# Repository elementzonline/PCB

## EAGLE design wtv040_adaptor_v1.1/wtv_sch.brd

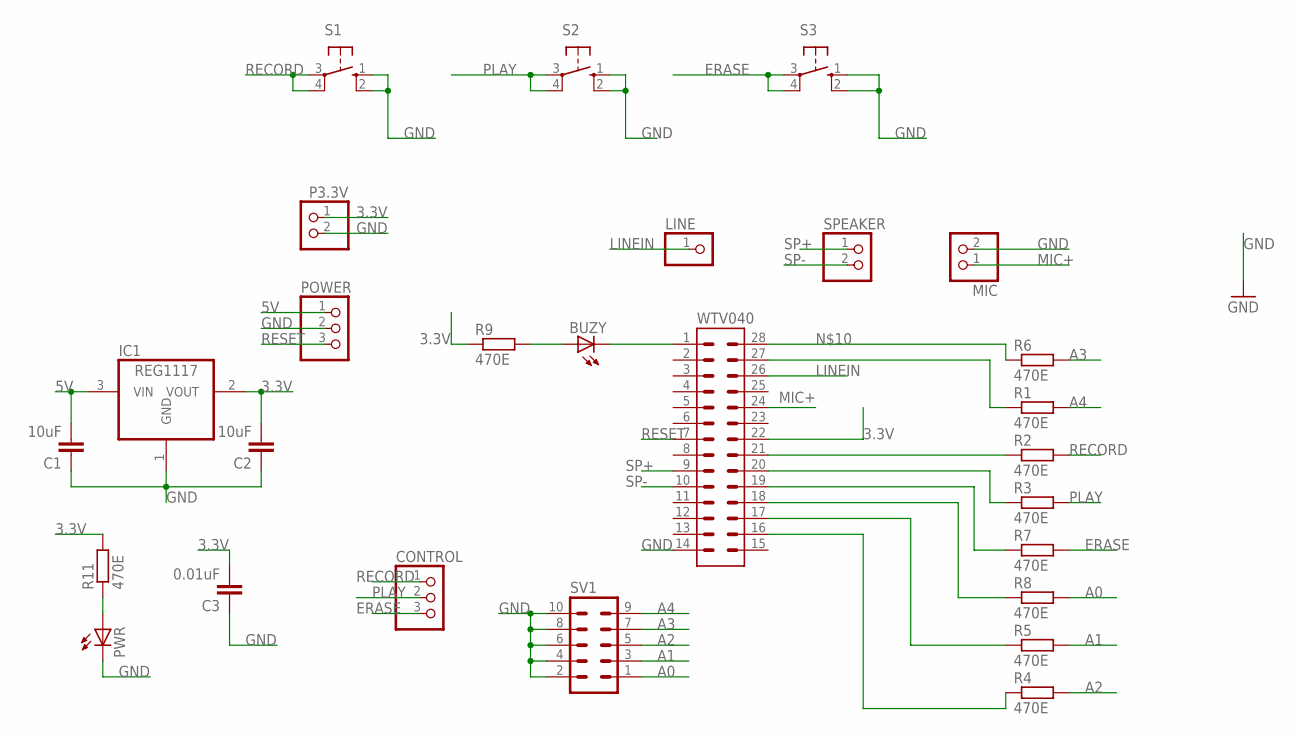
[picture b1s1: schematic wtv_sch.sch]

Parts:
BUZY: LEDSML0805; SML0805
C1, C2: 10uF; C0805
C3: 0.01uF; C0805
CONTROL: PINHD-1X3; 1X03
IC1: REG1117; SOT223
LINE: PINHD-1X1; 1X01
MIC: PINHD-1X2; 1X02
P3.3V: PINHD-1X2; 1X02
POWER: PINHD-1X3; 1X03
PWR: LEDSML0805; SML0805
R1, R2, R3, R4, R5, R6, R7, R8, R9, R11: 470E; R0805
S1, S2, S3: 10-XX; B3F-10XX
SPEAKER: PINHD-1X2; 1X02
SV1: MA05-2
WTV040: IC28P

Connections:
3.3V: C2.2, C3.2, IC1.2 (VOUT), P3.3V.1, R9.1, R11.2, WTV040.22
5V: C1.2, IC1.3 (VIN), POWER.1
A0: R8.2, SV1.1
A1: R5.2, SV1.3
A2: R4.2, SV1.5
A3: R6.2, SV1.7
A4: R1.2, SV1.9
ERASE: CONTROL.3, R7.2, S3.3, S3.4 (P1)
GND: C1.1, C2.1, C3.1, IC1.1 (GND), MIC.2, P3.3V.2, POWER.2, PWR.C, S1.1 (S), S1.2 (S1), S2.1 (S), S2.2 (S1), S3.1 (S), S3.2 (S1), SV1.2, SV1.4, SV1.6, SV1.8, SV1.10, WTV040.14
LINEIN: LINE.1, WTV040.26
MIC+: MIC.1, WTV040.24
unnamed: BUZY.A, R9.2
unnamed: BUZY.C, WTV040.1
unnamed: PWR.A, R11.1
unnamed: R6.1, WTV040.28
unnamed: R1.1, WTV040.27
unnamed: R4.1, WTV040.16
unnamed: R5.1, WTV040.17
unnamed: R8.1, WTV040.18
unnamed: R7.1, WTV040.19
unnamed: R3.1, WTV040.20
unnamed: R2.1, WTV040.21
PLAY: CONTROL.2, R3.2, S2.3, S2.4 (P1)
RECORD: CONTROL.1, R2.2, S1.3, S1.4 (P1)
RESET: POWER.3, WTV040.7
SP+: SPEAKER.1, WTV040.9
SP-: SPEAKER.2, WTV040.10

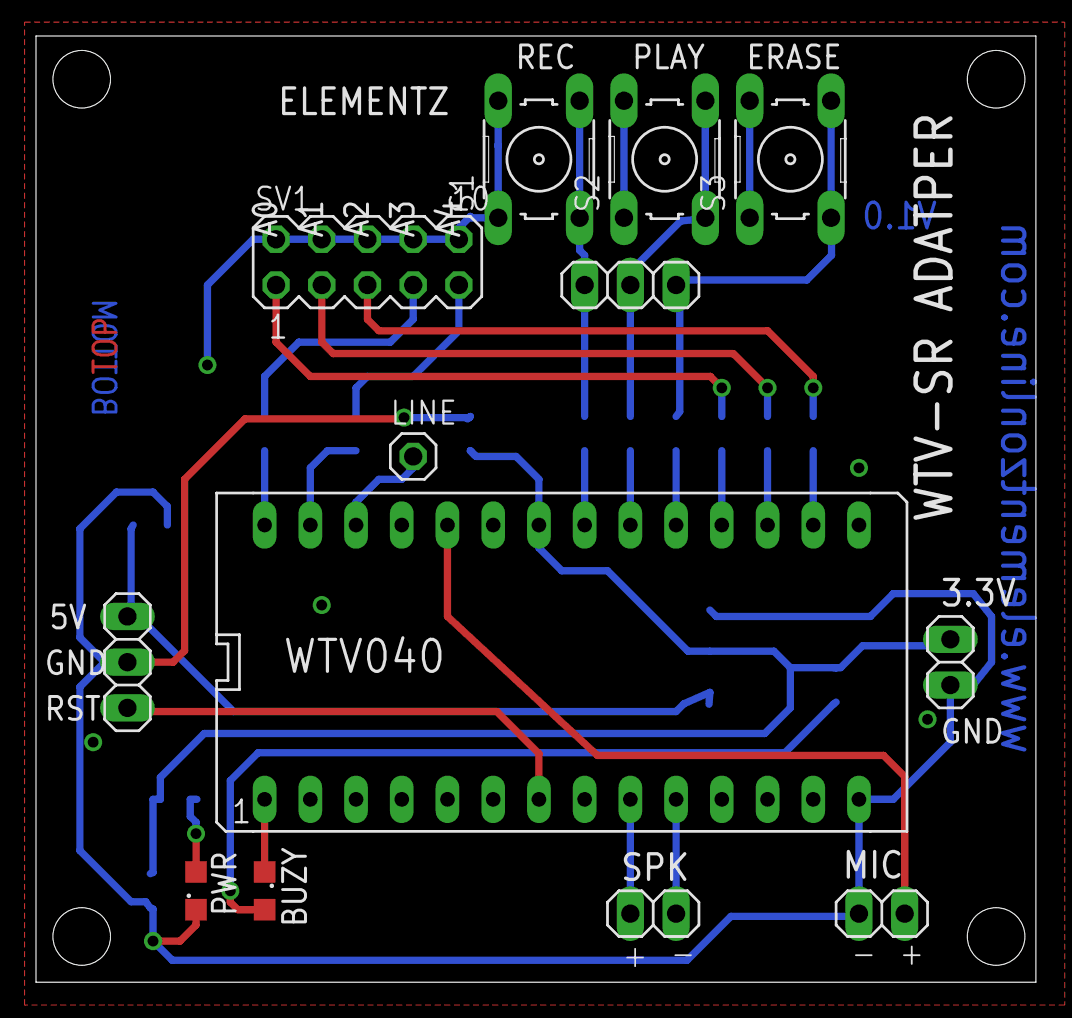
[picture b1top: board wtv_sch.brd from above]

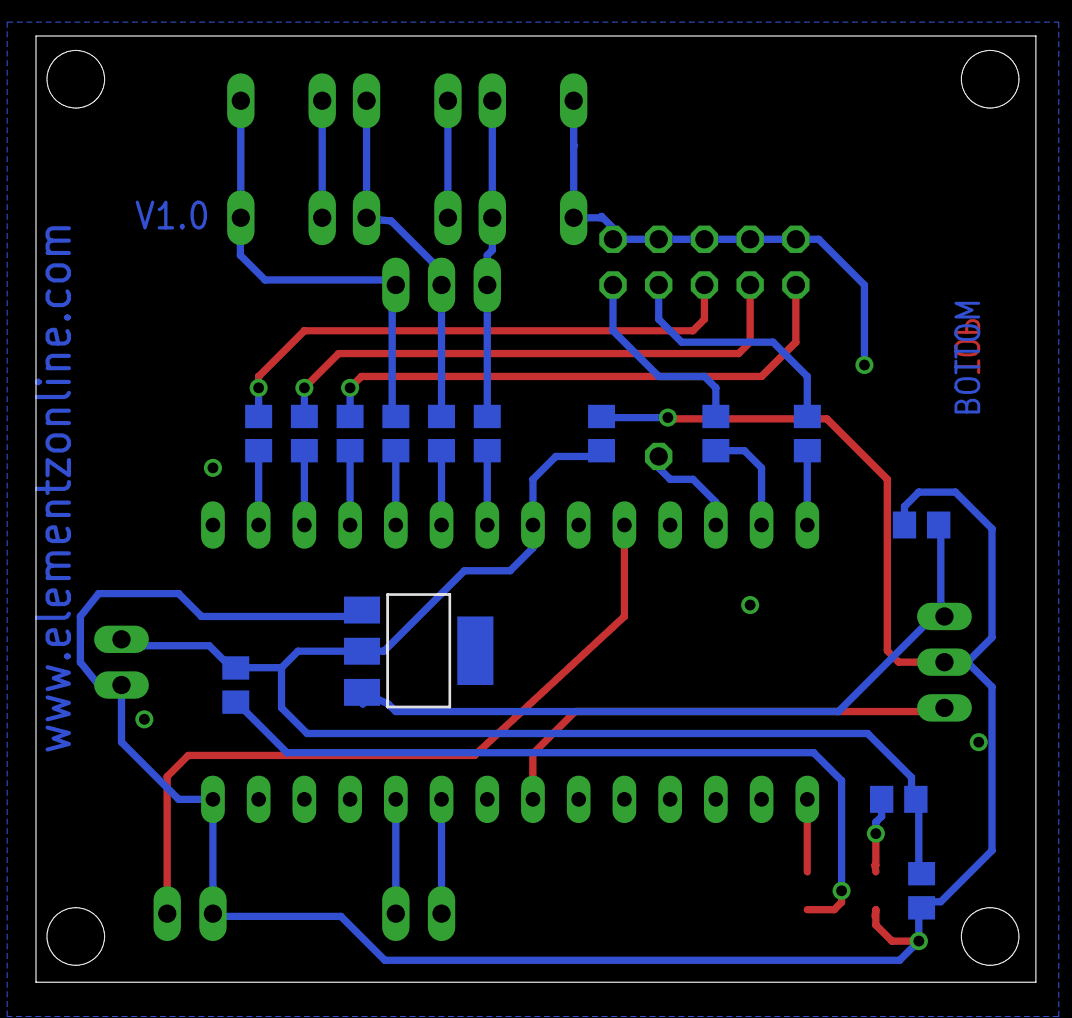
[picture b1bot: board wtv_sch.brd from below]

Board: 2 copper layers, 55.5 x 52.6 mm, 27 parts (14 on the bottom side), 27 nets.

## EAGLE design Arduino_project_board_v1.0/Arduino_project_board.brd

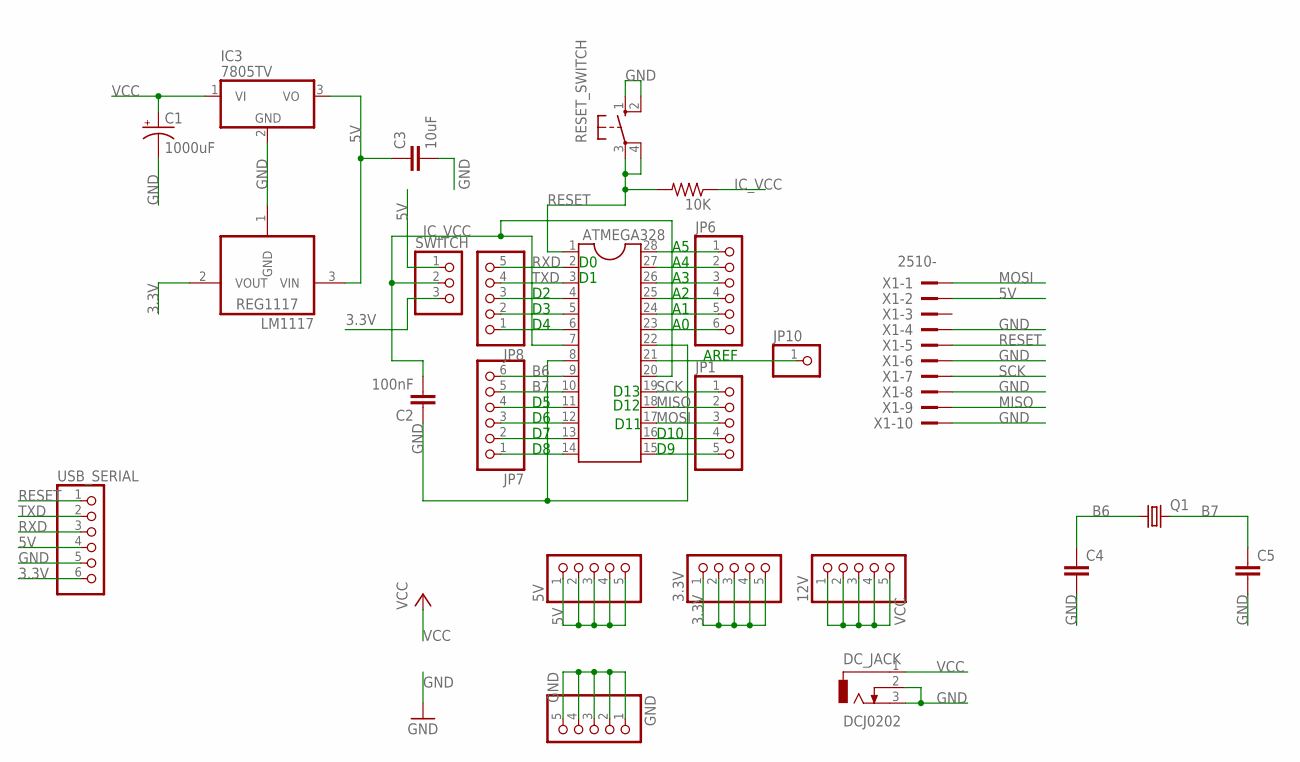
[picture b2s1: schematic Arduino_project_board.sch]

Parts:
3.3V, 5V, 12V: PINHD-1X5; 1X05
10K: R-US_R0805; R0805
ATMEGA328: DIL28-4
C1: 1000uF; CPOL-RADIAL-1000UF-25V
C2: 100nF; C0805K
C3: 10uF; C0805K
C4, C5: C-EUC0805K; C0805K
DC_JACK: DCJ0202
GND: PINHD-1X5; 1X05
IC3: 7805TV; TO220V
JP1, JP8: PINHD-1X5; 1X05
JP6, JP7: PINHD-1X6; 1X06
JP10: PINHD-1X1; 1X01
LM1117: REG1117; SOT223
Q1: CRYSTALHC49S; HC49/S
RESET_SWITCH: 10-XX; B3F-10XX
SWITCH: PINHD-1X3; 1X03
USB_SERIAL: PINHD-1X6; 1X06
X1: 2510-; PAK100/2500-10

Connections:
3.3V: 3.3V.1, 3.3V.2, 3.3V.3, 3.3V.4, 3.3V.5, LM1117.2 (VOUT), SWITCH.3, USB_SERIAL.6
5V: 5V.1, 5V.2, 5V.3, 5V.4, 5V.5, C3.1, IC3.3 (VO), LM1117.3 (VIN), SWITCH.1, USB_SERIAL.4, X1.2
B6: ATMEGA328.9, C4.1, JP7.6, Q1.1
B7: ATMEGA328.10, C5.1, JP7.5, Q1.2
GND: ATMEGA328.8, ATMEGA328.22, C1.-, C2.1, C3.2, C4.2, C5.2, DC_JACK.2, DC_JACK.3, GND.1, GND.2, GND.3, GND.4, GND.5, IC3.2 (GND), LM1117.1 (GND), RESET_SWITCH.1 (S), RESET_SWITCH.2 (S1), USB_SERIAL.5, X1.4, X1.6, X1.8, X1.10
IC_VCC: 10K.1, ATMEGA328.7, ATMEGA328.20, C2.2, SWITCH.2
MISO: ATMEGA328.18, JP1.2, X1.9
MOSI: ATMEGA328.17, JP1.3, X1.1
unnamed: ATMEGA328.28, JP6.1
unnamed: ATMEGA328.27, JP6.2
unnamed: ATMEGA328.26, JP6.3
unnamed: ATMEGA328.25, JP6.4
unnamed: ATMEGA328.24, JP6.5
unnamed: ATMEGA328.23, JP6.6
unnamed: ATMEGA328.15, JP1.5
unnamed: ATMEGA328.16, JP1.4
unnamed: ATMEGA328.21, JP10.1
unnamed: ATMEGA328.4, JP8.3
unnamed: ATMEGA328.5, JP8.2
unnamed: ATMEGA328.6, JP8.1
unnamed: ATMEGA328.11, JP7.4
unnamed: ATMEGA328.12, JP7.3
unnamed: ATMEGA328.13, JP7.2
unnamed: ATMEGA328.14, JP7.1
RESET: 10K.2, ATMEGA328.1, RESET_SWITCH.3, RESET_SWITCH.4 (P1), USB_SERIAL.1, X1.5
RXD: ATMEGA328.2, JP8.5, USB_SERIAL.3
SCK: ATMEGA328.19, JP1.1, X1.7
TXD: ATMEGA328.3, JP8.4, USB_SERIAL.2
VCC: 12V.1, 12V.2, 12V.3, 12V.4, 12V.5, C1.+, DC_JACK.1, IC3.1 (VI)

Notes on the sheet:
D10
D11
D12
D13
AREF

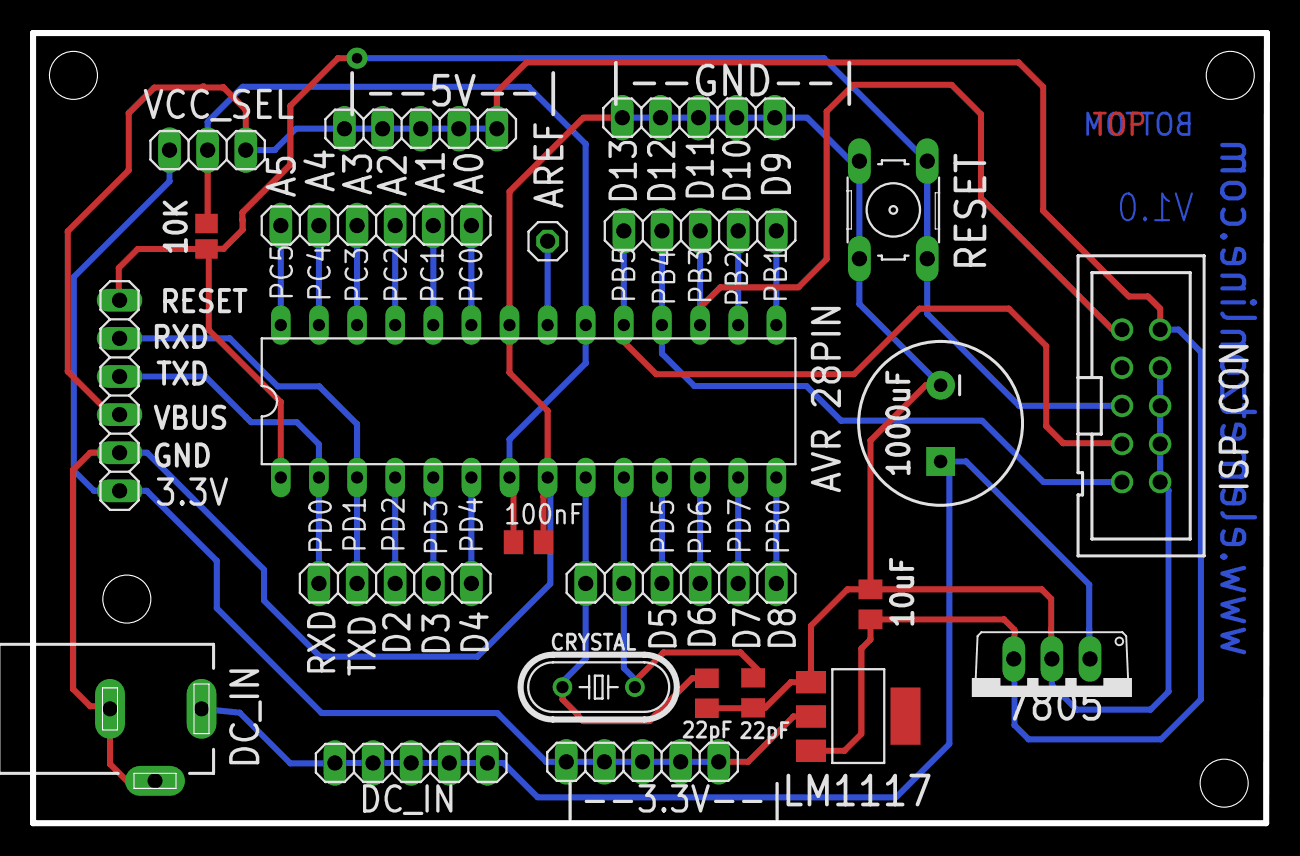
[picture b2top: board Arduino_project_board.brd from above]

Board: 2 copper layers, 82.2 x 52.7 mm, 24 parts (0 on the bottom side), 29 nets.

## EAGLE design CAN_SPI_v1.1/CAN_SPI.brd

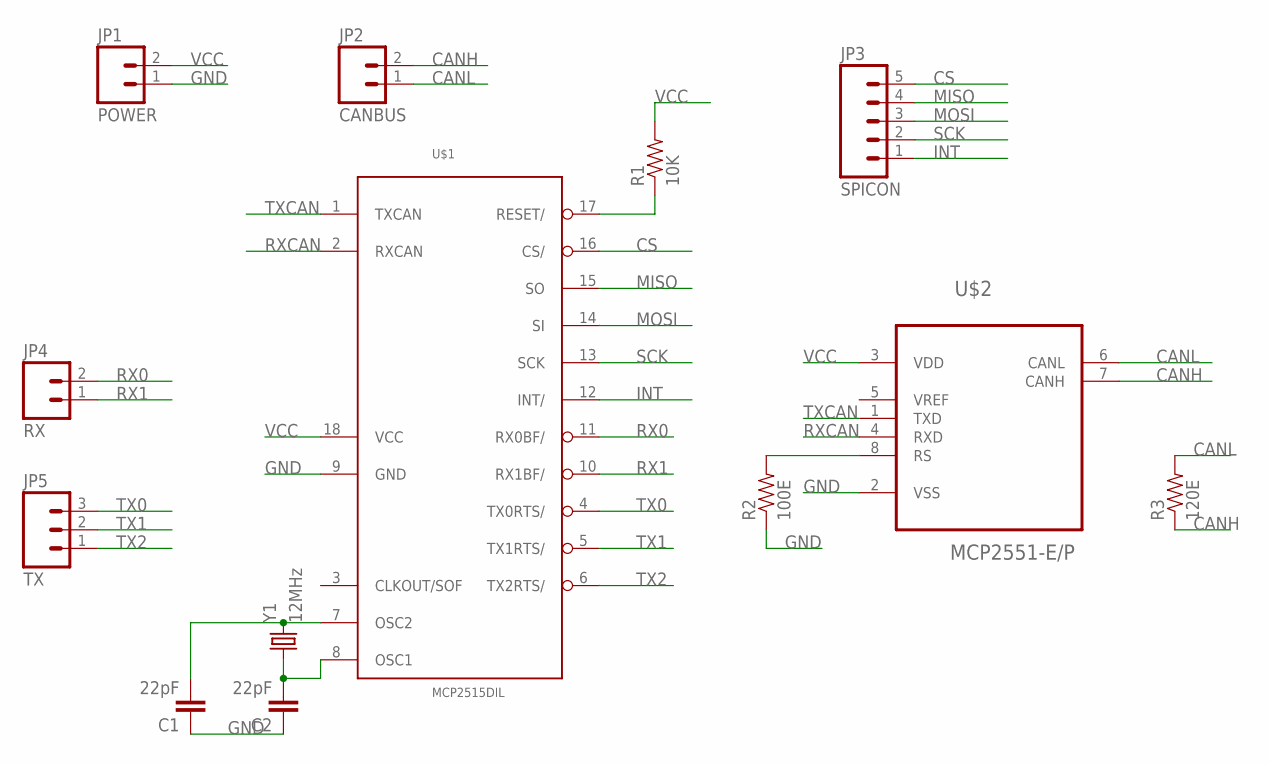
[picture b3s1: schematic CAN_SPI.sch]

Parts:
C1, C2: 22pF; CAP-PTH-SMALL-KIT
JP1: POWER; 1X02_LONGPADS
JP2: CANBUS; 1X02_LONGPADS
JP3: SPICON; 1X05_LONGPADS
JP4: RX; 1X02_LONGPADS
JP5: TX; 1X03_LONGPADS
R1: 10K; AXIAL-0.3
R2: 100E; AXIAL-0.3
R3: 120E; AXIAL-0.3
U$1: MCP2515DIL; DIL18
U$2: MCP2551-E/P; DIP254P762X432-8
Y1: 12MHz; HC49US

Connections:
CANH: JP2.2, R3.P$1 (1), U$2.7 (CANH)
CANL: JP2.1, R3.P$2 (2), U$2.6 (CANL)
CS: JP3.5, U$1.16 (CS/)
GND: C1.1, C2.1, JP1.1, R2.P$1 (1), U$1.9 (GND), U$2.2 (VSS)
INT: JP3.1, U$1.12 (INT/)
MISO: JP3.4, U$1.15 (SO)
MOSI: JP3.3, U$1.14 (SI)
unnamed: R1.P$1 (1), U$1.17 (RESET/)
unnamed: C1.2, U$1.7 (OSC2), Y1.2
unnamed: C2.2, U$1.8 (OSC1), Y1.1
unnamed: R2.P$2 (2), U$2.8 (RS)
RX0: JP4.2, U$1.11 (RX0BF/)
RX1: JP4.1, U$1.10 (RX1BF/)
RXCAN: U$1.2 (RXCAN), U$2.4 (RXD)
SCK: JP3.2, U$1.13 (SCK)
TX0: JP5.3, U$1.4 (TX0RTS/)
TX1: JP5.2, U$1.5 (TX1RTS/)
TX2: JP5.1, U$1.6 (TX2RTS/)
TXCAN: U$1.1 (TXCAN), U$2.1 (TXD)
VCC: JP1.2, R1.P$2 (2), U$1.18 (VCC), U$2.3 (VDD)

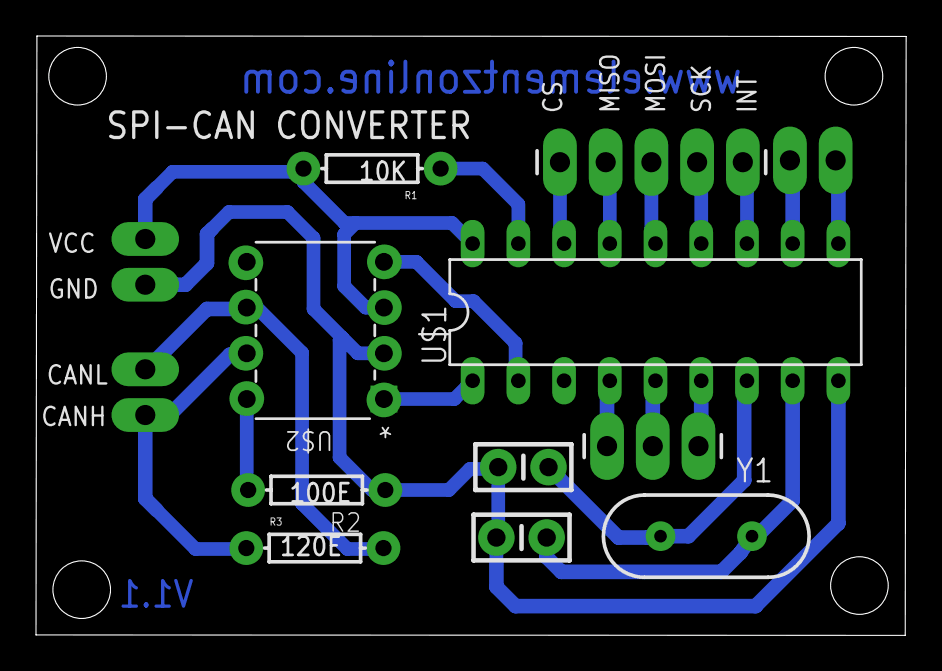
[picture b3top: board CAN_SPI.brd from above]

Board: 2 copper layers, 48.3 x 33.3 mm, 13 parts (0 on the bottom side), 20 nets.

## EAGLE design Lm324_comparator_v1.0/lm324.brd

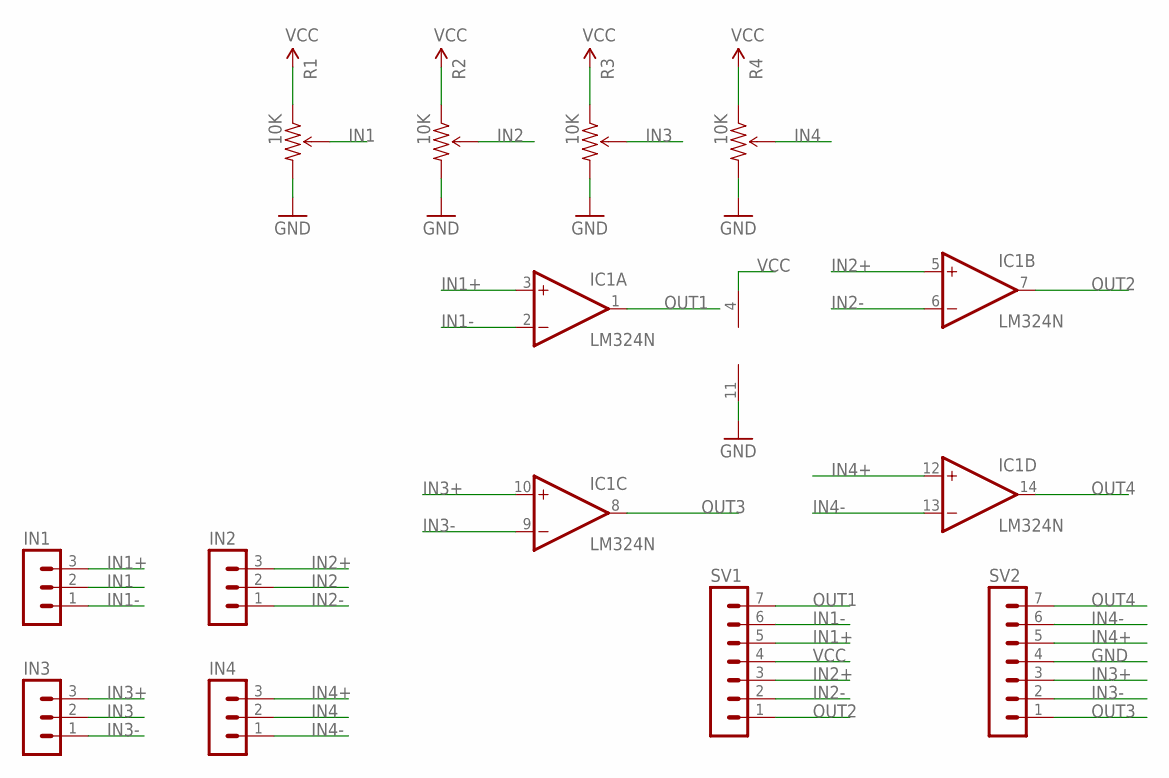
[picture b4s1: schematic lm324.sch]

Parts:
IC1: LM324N; DIL14
IN1, IN2, IN3, IN4: MA03-1
R1, R2, R3, R4: 10K; TRIM_POT_PTH
SV1, SV2: MA07-1

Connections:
GND: IC1.11 (V-), R1.3 (CW), R2.3 (CW), R3.3 (CW), R4.3 (CW), SV2.4
IN1: IN1.2, R1.2 (WIPER)
IN1+: IC1.3 (+IN), IN1.3, SV1.5
IN1-: IC1.2 (-IN), IN1.1, SV1.6
IN2: IN2.2, R2.2 (WIPER)
IN2+: IC1.5 (+IN), IN2.3, SV1.3
IN2-: IC1.6 (-IN), IN2.1, SV1.2
IN3: IN3.2, R3.2 (WIPER)
IN3+: IC1.10 (+IN), IN3.3, SV2.3
IN3-: IC1.9 (-IN), IN3.1, SV2.2
IN4: IN4.2, R4.2 (WIPER)
IN4+: IC1.12 (+IN), IN4.3, SV2.5
IN4-: IC1.13 (-IN), IN4.1, SV2.6
OUT1: IC1.1 (OUT), SV1.7
OUT2: IC1.7 (OUT), SV1.1
OUT3: IC1.8 (OUT), SV2.1
OUT4: IC1.14 (OUT), SV2.7
VCC: IC1.4 (V+), R1.1 (CCW), R2.1 (CCW), R3.1 (CCW), R4.1 (CCW), SV1.4

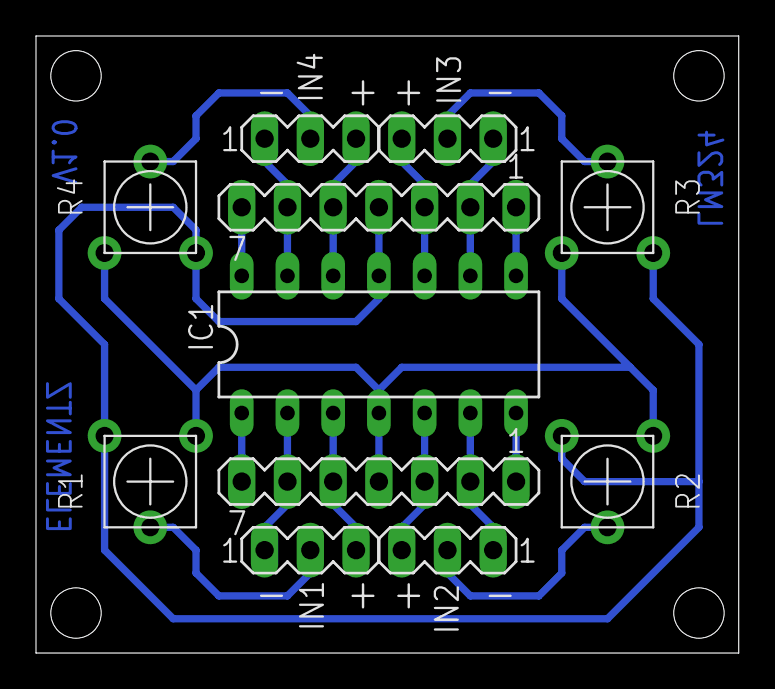
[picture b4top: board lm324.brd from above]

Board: 2 copper layers, 39.0 x 34.3 mm, 11 parts (0 on the bottom side), 18 nets.

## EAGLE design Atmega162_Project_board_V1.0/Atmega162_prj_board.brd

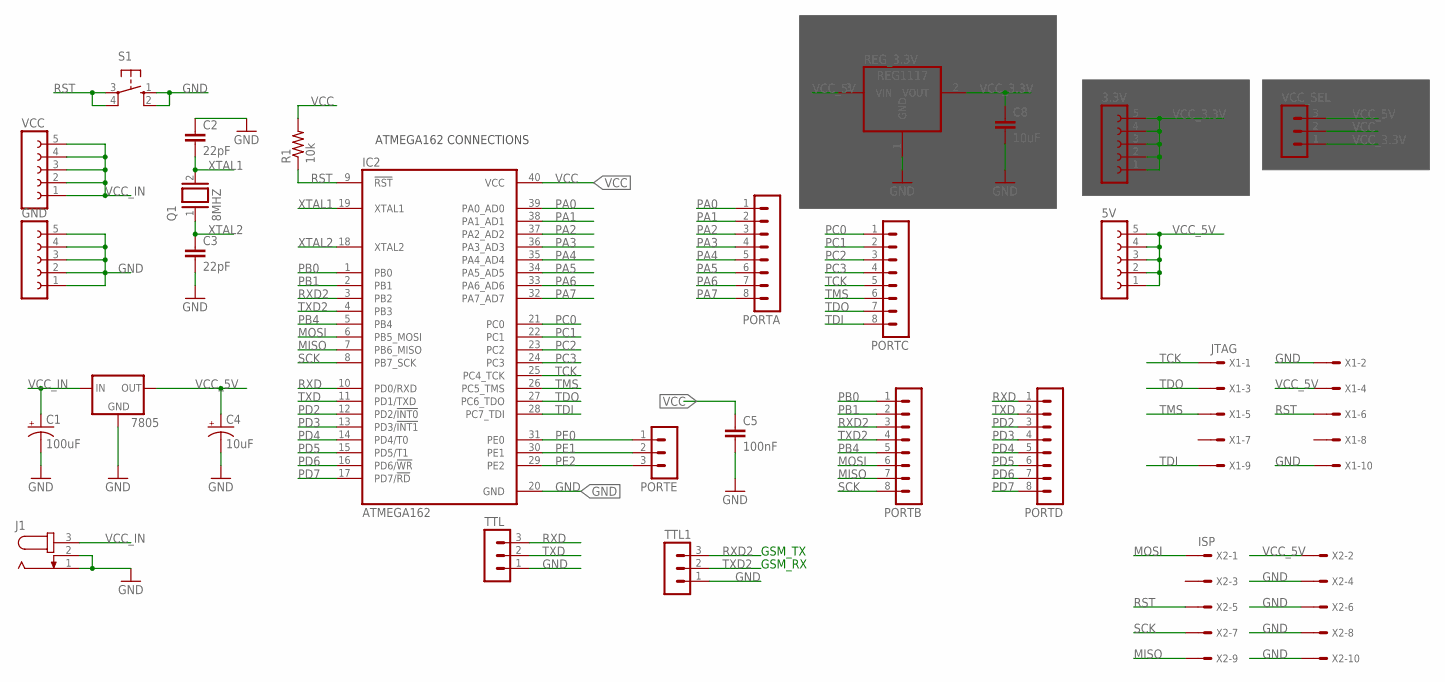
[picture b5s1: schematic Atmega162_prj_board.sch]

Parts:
3.3V, 5V: FE05-1
7805: 78XXS
C1: 100uF; CPOL-RADIAL-100UF-25V
C2, C3: 22pF; CAP-PTH-SMALLEZ
C4: 10uF; CPOL-RADIAL-10UF-25V
C5: 100nF; 0805
C8: 10uF; 0805
GND: FE05-1
IC2: ATMEGA162; DIL40
J1: JACK-PLUG0; SPC4077
PORTA: MA08-1
PORTB: MA08-1
PORTC: MA08-1
PORTD: MA08-1
PORTE: MA03-1
Q1: 8MHZ; QS
R1: 10k; AXIAL-0.3
REG_3.3V: REG1117; SOT223
S1: 10-XX; B3F-10XX
TTL, TTL1: MA03-1
VCC: FE05-1
VCC_SEL: MA03-1
X1: JTAG; 057-010-1
X2: ISP; 057-010-1

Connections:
GND: 7805.GND, C1.2 (-), C2.1, C3.2, C4.2 (-), C5.2, C8.2, GND.1, GND.2, GND.3, GND.4, GND.5, IC2.20 (GND), J1.1, J1.2, REG_3.3V.1 (GND), S1.1 (S), S1.2 (S1), TTL.1, TTL1.1, X1.2, X1.10, X2.4, X2.6, X2.8, X2.10
MISO: IC2.7 (PB6_MISO), PORTB.7, X2.9
MOSI: IC2.6 (PB5_MOSI), PORTB.6, X2.1
PA0: IC2.39 (PA0_AD0), PORTA.1
PA1: IC2.38 (PA1_AD1), PORTA.2
PA2: IC2.37 (PA2_AD2), PORTA.3
PA3: IC2.36 (PA3_AD3), PORTA.4
PA4: IC2.35 (PA4_AD4), PORTA.5
PA5: IC2.34 (PA5_AD5), PORTA.6
PA6: IC2.33 (PA6_AD6), PORTA.7
PA7: IC2.32 (PA7_AD7), PORTA.8
PB0: IC2.1 (PB0), PORTB.1
PB1: IC2.2 (PB1), PORTB.2
PB4: IC2.5 (PB4), PORTB.5
PC0: IC2.21 (PC0), PORTC.1
PC1: IC2.22 (PC1), PORTC.2
PC2: IC2.23 (PC2), PORTC.3
PC3: IC2.24 (PC3), PORTC.4
PD2: IC2.12 (PD2/!INT0), PORTD.3
PD3: IC2.13 (PD3/!INT1), PORTD.4
PD4: IC2.14 (PD4/T0), PORTD.5
PD5: IC2.15 (PD5/T1), PORTD.6
PD6: IC2.16 (PD6/!WR), PORTD.7
PD7: IC2.17 (PD7/!RD), PORTD.8
PE0: IC2.31 (PE0), PORTE.1
PE1: IC2.30 (PE1), PORTE.2
PE2: IC2.29 (PE2), PORTE.3
RST: IC2.9 (!RST), R1.P$1 (1), S1.3, S1.4 (P1), X1.6, X2.5
RXD: IC2.10 (PD0/RXD), PORTD.1, TTL.3
RXD2: IC2.3 (PB2), PORTB.3, TTL1.3
SCK: IC2.8 (PB7_SCK), PORTB.8, X2.7
TCK: IC2.25 (PC4_TCK), PORTC.5, X1.1
TDI: IC2.28 (PC7_TDI), PORTC.8, X1.9
TDO: IC2.27 (PC6_TDO), PORTC.7, X1.3
TMS: IC2.26 (PC5_TMS), PORTC.6, X1.5
TXD: IC2.11 (PD1/TXD), PORTD.2, TTL.2
TXD2: IC2.4 (PB3), PORTB.4, TTL1.2
VCC: C5.1, IC2.40 (VCC), R1.P$2 (2), VCC_SEL.2
VCC_3.3V: 3.3V.1, 3.3V.2, 3.3V.3, 3.3V.4, 3.3V.5, C8.1, REG_3.3V.2 (VOUT), VCC_SEL.1
VCC_5V: 5V.1, 5V.2, 5V.3, 5V.4, 5V.5, 7805.OUT, C4.1 (+), REG_3.3V.3 (VIN), VCC_SEL.3, X1.4, X2.2
VCC_IN: 7805.IN, C1.1 (+), J1.3, VCC.1, VCC.2, VCC.3, VCC.4, VCC.5
XTAL1: C2.2, IC2.19 (XTAL1), Q1.2
XTAL2: C3.1, IC2.18 (XTAL2), Q1.1

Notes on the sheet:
ATMEGA162 CONNECTIONS
GSM_TX
GSM_RX

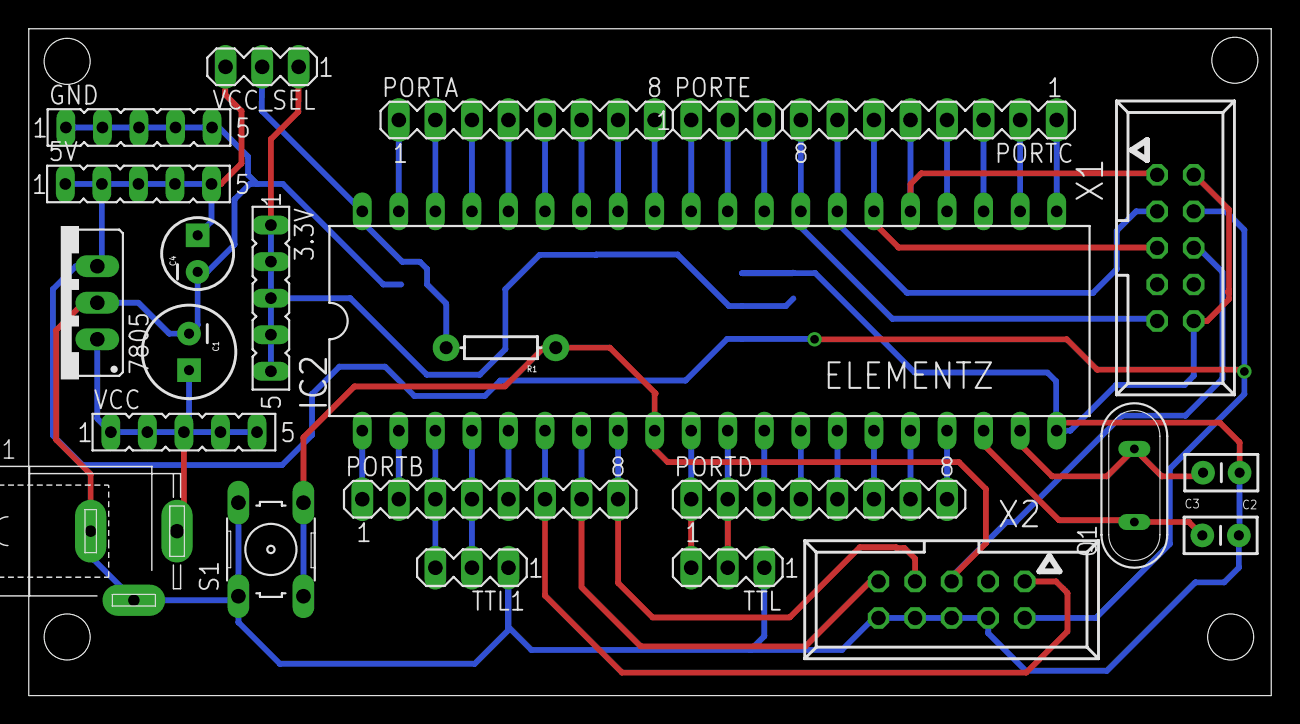
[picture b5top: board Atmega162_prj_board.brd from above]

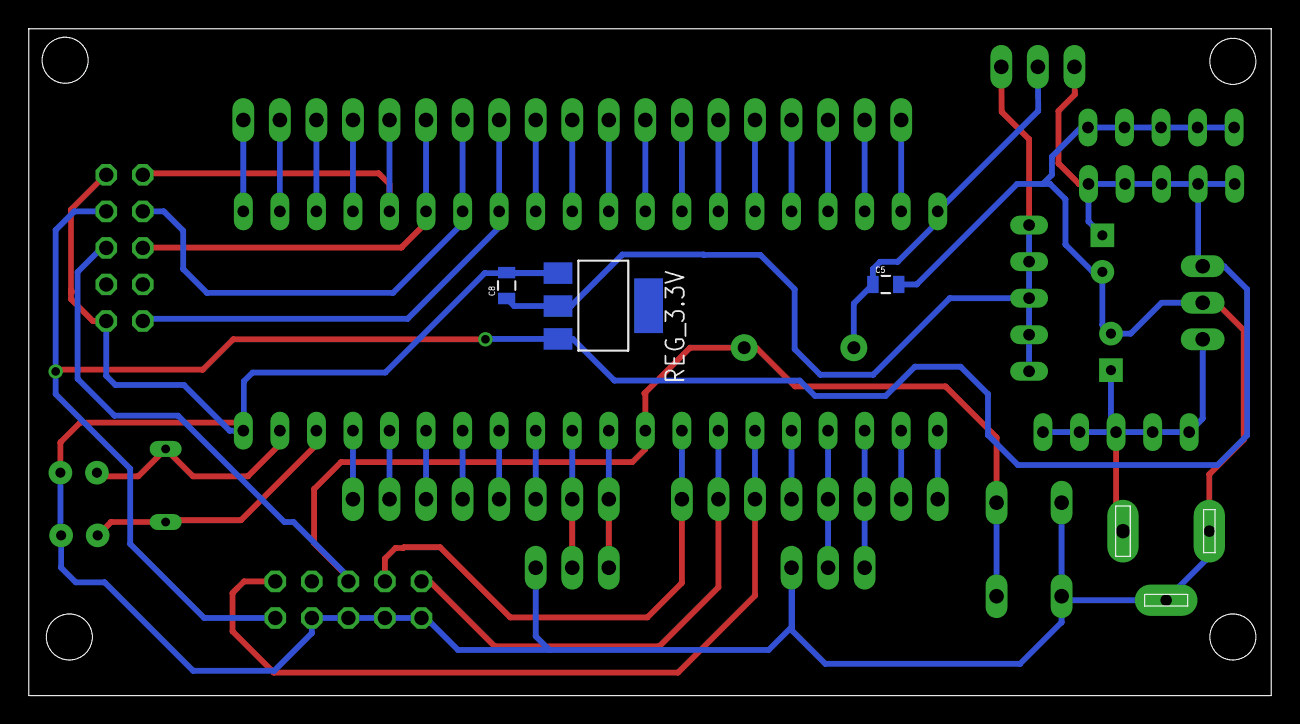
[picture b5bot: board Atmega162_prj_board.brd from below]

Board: 2 copper layers, 86.3 x 46.3 mm, 27 parts (3 on the bottom side), 43 nets.

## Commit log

2015-03-26 By Dhanish

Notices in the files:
parts and their libraries:
SparkFun-Capacitors: Licensing: Creative Commons ShareAlike 4.0 International - https://creativecommons.org/licenses/by-sa/4.0
